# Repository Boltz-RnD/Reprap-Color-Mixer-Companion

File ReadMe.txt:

RCMC

RepRap Color Mixer Companion

"RCMC Gen 1" Is an External I2C Module, which is Developed to control the color output on a color Mixing hotend.

The hex code of the color output required is sent through i2c port and the RCMC automatically tunes the flow rate of the colors Cyan,Yellow,Margenta, White and black, to give the respective output.

RCMC has two Connectors which connects to the driver board

1.Stepper Driver connector shield
   
This shield Connector fits upon your printer board's(eg. RAMPS) extruder's stepper driver's connector and recieves the steps (signal) sent by the printer board.

2.I2C Connector

This Connector is used by RCMC to recieve the color command.

The CPU, based on the color Selected and Stepper driver's signal pulses calculates the resultant flow rates for diffrent Colors , and hence we get multicolor output.

We made this device as a companion to our 1st Gen Hotend and was closed source first, but since we also started by using reprap designs and the community's help, we decided to make RCMC open Source and give something back to the Community.

Feel free to contribute,remix,improve and adapt this work :) .

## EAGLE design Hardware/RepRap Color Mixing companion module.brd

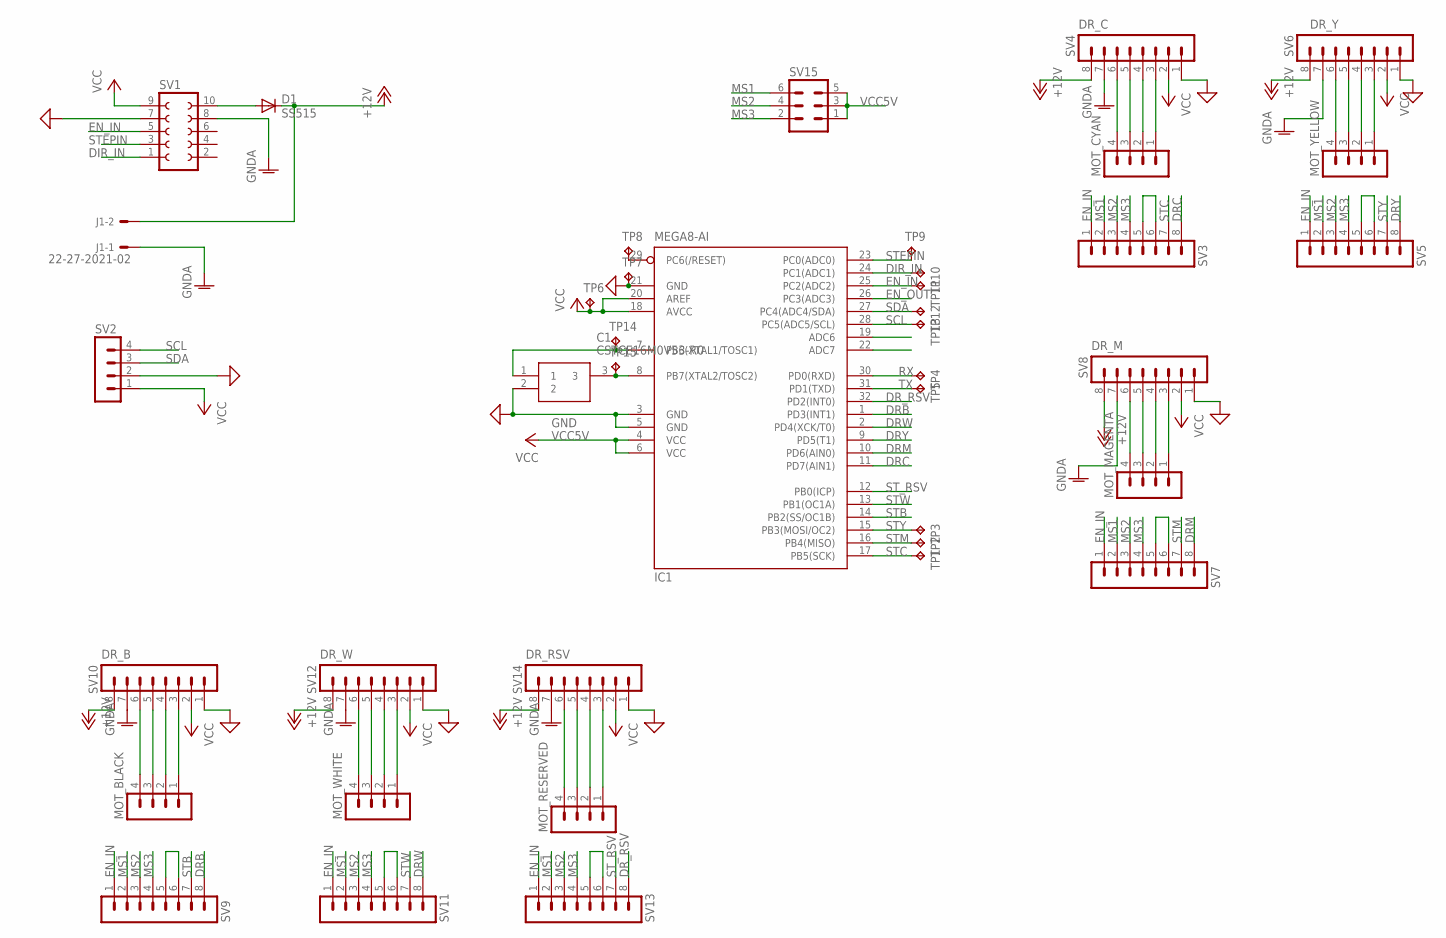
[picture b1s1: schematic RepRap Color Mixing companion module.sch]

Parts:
C1: CSTCE16M0V53-R0; CSTCE-V
D1: SS515; SMC
IC1: MEGA8-AI; TQFP32-08
J1: 22-27-2021-02; 6410-02
MOT_BLACK: MA04-1
MOT_CYAN: MA04-1
MOT_MAGENTA: MA04-1
MOT_RESERVED: MA04-1
MOT_WHITE: MA04-1
MOT_YELLOW: MA04-1
SV1: FE05-2
SV2: MA04-1
SV3, SV4, SV5, SV6, SV7, SV8, SV9, SV10, SV11, SV12, SV13, SV14: MA08-1
SV15: MA03-2
TP1, TP2, TP3, TP4, TP5, TP6, TP7, TP8, TP9, TP10, TP11, TP12, TP13, TP14, TP15: TPB1,27; B1,27

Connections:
+12V: D1.C, J1.2, SV4.8, SV6.8, SV8.8, SV10.8, SV12.8, SV14.8
DIR_IN: IC1.24 (PC1(ADC1)), SV1.1, TP10.TP
DRB: IC1.1 (PD3(INT1)), SV9.8
DRC: IC1.11 (PD7(AIN1)), SV3.8
DRM: IC1.10 (PD6(AIN0)), SV7.8
DRW: IC1.2 (PD4(XCK/T0)), SV11.8
DRY: IC1.9 (PD5(T1)), SV5.8
DR_RSV: IC1.32 (PD2(INT0)), SV13.8
EN_IN: IC1.25 (PC2(ADC2)), SV1.5, SV3.1, SV5.1, SV7.1, SV9.1, SV11.1, SV13.1, TP11.TP
EN_OUT: IC1.26 (PC3(ADC3))
GND: C1.2, IC1.3 (GND), IC1.5 (GND), IC1.21 (GND), SV1.7, SV2.2, SV4.1, SV6.1, SV8.1, SV10.1, SV12.1, SV14.1, TP7.TP
GNDA: J1.1, SV1.8, SV4.7, SV6.7, SV8.7, SV10.7, SV12.7, SV14.7
MS1: SV3.2, SV5.2, SV7.2, SV9.2, SV11.2, SV13.2, SV15.6
MS2: SV3.3, SV5.3, SV7.3, SV9.3, SV11.3, SV13.3, SV15.4
MS3: SV3.4, SV5.4, SV7.4, SV9.4, SV11.4, SV13.4, SV15.2
unnamed: C1.3, IC1.8 (PB7(XTAL2/TOSC2)), TP15.TP
unnamed: C1.1, IC1.7 (PB6(XTAL1/TOSC1)), TP14.TP
unnamed: IC1.29 (PC6(/RESET)), TP8.TP
unnamed: D1.A, SV1.10
unnamed: SV3.5, SV3.6
unnamed: MOT_CYAN.1, SV4.3
unnamed: MOT_CYAN.2, SV4.4
unnamed: MOT_CYAN.3, SV4.5
unnamed: MOT_CYAN.4, SV4.6
unnamed: SV5.5, SV5.6
unnamed: MOT_YELLOW.1, SV6.3
unnamed: MOT_YELLOW.2, SV6.4
unnamed: MOT_YELLOW.3, SV6.5
unnamed: MOT_YELLOW.4, SV6.6
unnamed: SV7.5, SV7.6
unnamed: MOT_MAGENTA.1, SV8.3
unnamed: MOT_MAGENTA.2, SV8.4
unnamed: MOT_MAGENTA.3, SV8.5
unnamed: MOT_MAGENTA.4, SV8.6
unnamed: SV9.5, SV9.6
unnamed: MOT_BLACK.1, SV10.3
unnamed: MOT_BLACK.2, SV10.4
unnamed: MOT_BLACK.3, SV10.5
unnamed: MOT_BLACK.4, SV10.6
unnamed: SV11.5, SV11.6
unnamed: MOT_WHITE.1, SV12.3
unnamed: MOT_WHITE.2, SV12.4
unnamed: MOT_WHITE.3, SV12.5
unnamed: MOT_WHITE.4, SV12.6
unnamed: SV13.5, SV13.6
unnamed: MOT_RESERVED.1, SV14.3
unnamed: MOT_RESERVED.2, SV14.4
unnamed: MOT_RESERVED.3, SV14.5
unnamed: MOT_RESERVED.4, SV14.6
RX: IC1.30 (PD0(RXD)), TP4.TP
SCL: IC1.28 (PC5(ADC5/SCL)), SV2.4, TP13.TP
SDA: IC1.27 (PC4(ADC4/SDA)), SV2.3, TP12.TP
STB: IC1.14 (PB2(SS/OC1B)), SV9.7
STC: IC1.17 (PB5(SCK)), SV3.7, TP1.TP
STEPIN: IC1.23 (PC0(ADC0)), SV1.3, TP9.TP
STM: IC1.16 (PB4(MISO)), SV7.7, TP2.TP
STW: IC1.13 (PB1(OC1A)), SV11.7
STY: IC1.15 (PB3(MOSI/OC2)), SV5.7, TP3.TP
ST_RSV: IC1.12 (PB0(ICP)), SV13.7
TX: IC1.31 (PD1(TXD)), TP5.TP
VCC: IC1.18 (AVCC), IC1.20 (AREF), SV1.9, SV2.1, SV4.2, SV6.2, SV8.2, SV10.2, SV12.2, SV14.2, TP6.TP
VCC5V: IC1.4 (VCC), IC1.6 (VCC), SV15.1, SV15.3, SV15.5

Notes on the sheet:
DR_C
DR_Y
DR_M
DR_B
DR_W
DR_RSV

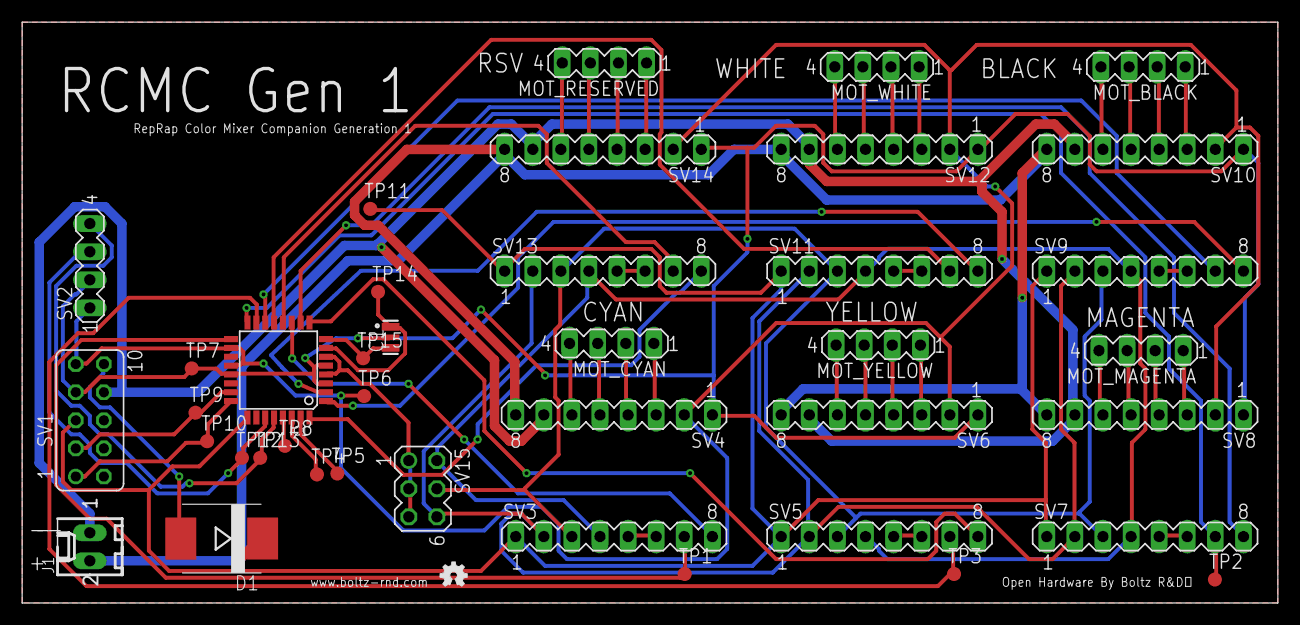
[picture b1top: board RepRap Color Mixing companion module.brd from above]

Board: 2 copper layers, 113.5 x 52.5 mm, 41 parts (0 on the bottom side), 61 nets.

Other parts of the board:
U$2: OSHW-LOGO-MINI

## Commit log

2018-06-20 Added Files
    Added Board file and Schematics Files
2018-06-20 Corrected Readme's Format
2019-01-01 Organized Folders and Added CAD Files of MFDS
    Organized Folders and Added CAD Files of Multiple Filament Delivery System.

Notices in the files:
parts and their libraries:
SparkFun-Aesthetics: Licensing: Creative Commons ShareAlike 4.0 International - https://creativecommons.org/licenses/by-sa/4.0
